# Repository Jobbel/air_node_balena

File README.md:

# air_node
 Software package and hardware for a BalenaOS based air quality sensor node featuring cellular networking, 
 MQTT, GPS localisation, local USB drive data logging and support for the following sensors:
 
 - Alphasense OPC-N3 PM Sensor
 - 2xADS1115 connected to NO-B4,CO-B4,OX-B431,NO2-B43 Alphasense ISBs
 - HYT221 Temperature/Humidity Sensor
 - SHT3x Temperature/Humidity Sensor

Hardware used during developement:

 - Raspberry Pi 4
 - SIM7600 4G Modem/GPS receiver
 - USB Stick for local data storage (needs to be vfat formatted)

Configuration can be done via BalenaCloud environment variables or in src/config_cloudless.py if no cloud will be used.

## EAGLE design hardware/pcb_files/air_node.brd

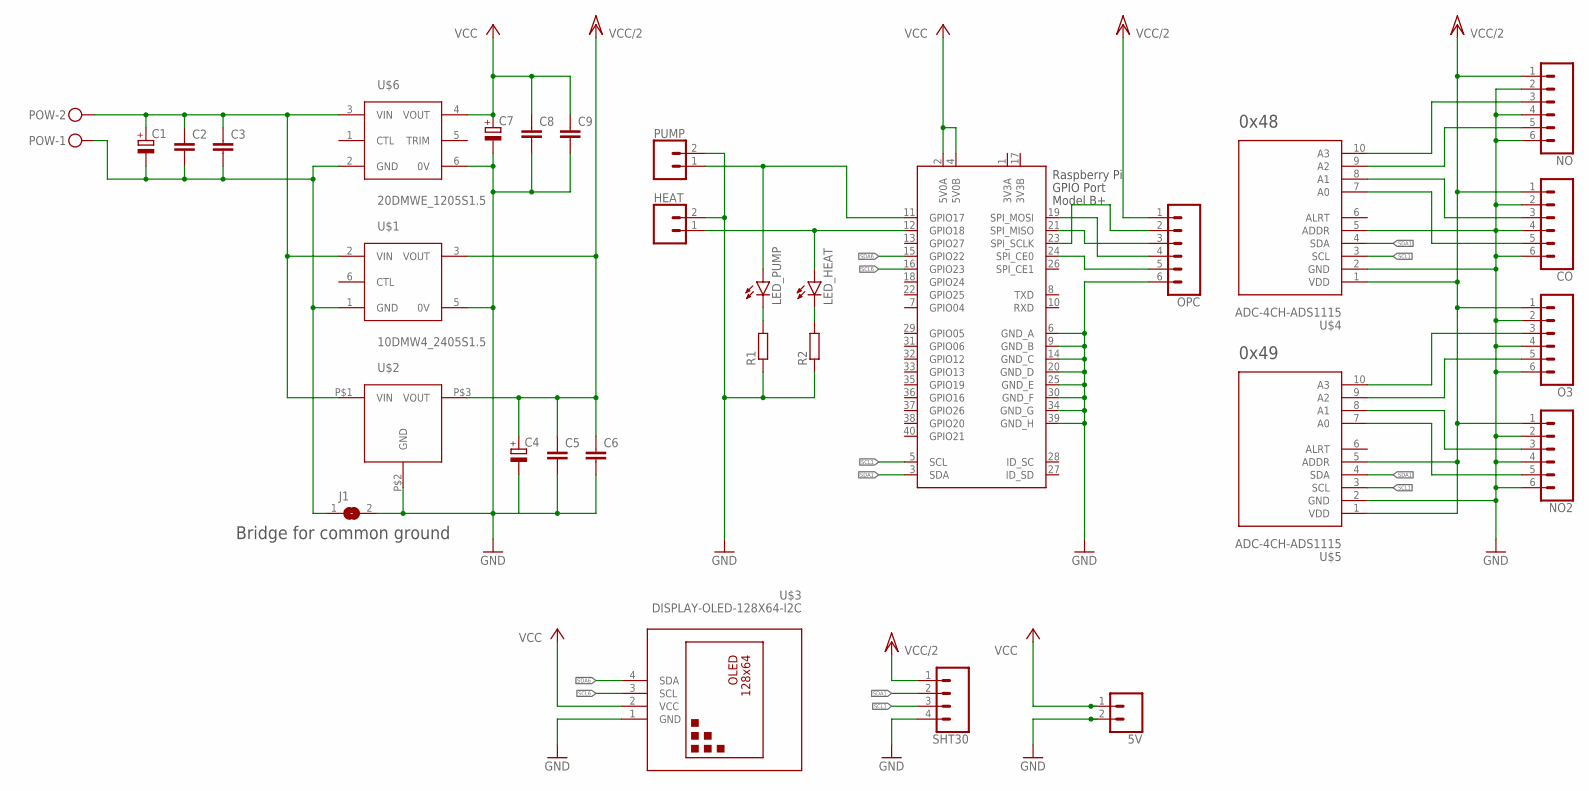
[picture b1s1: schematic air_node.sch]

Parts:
5V: CONN_021X02_NO_SILK; 1X02_NO_SILK
C1, C4, C7: CPOL-EUE3.5-10; E3,5-10
C2, C5, C8: C-EUC1206; C1206
C3, C6, C9: C-EUC0805; C0805
CO: CONN_06NO_SILK_FEMALE_PTH; 1X06_NO_SILK
HEAT: CONN_021X02_NO_SILK; 1X02_NO_SILK
J1: SJ
LED_HEAT: LEDCHIP-LED0805; CHIP-LED0805
LED_PUMP: LEDCHIP-LED0805; CHIP-LED0805
NO, NO2: CONN_06NO_SILK_FEMALE_PTH; 1X06_NO_SILK
O3: CONN_06NO_SILK_FEMALE_PTH; 1X06_NO_SILK
OPC: CONN_06NO_SILK_FEMALE_PTH; 1X06_NO_SILK
POW: MKDSN1,5/2-5,08
PUMP: CONN_021X02_NO_SILK; 1X02_NO_SILK
R1, R2: R-EU_R0805; R0805
SHT30: CONN_041X04_NO_SILK; 1X04_NO_SILK
U$1: 10DMW4_2405S1.5
U$2: LME78_05-1.0
U$3: DISPLAY-OLED-128X64-I2C
U$4, U$5: ADC-4CH-ADS1115
U$6: 20DMWE_1205S1.5
X1: RASPI_BOARD_B+#_E4; RASPI_BOARD_B+_EDGES_4DRILL

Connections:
3V3A: X1.1 (3V3A)
3V3B: X1.17 (3V3B)
12VGND: C1.-, C2.2, C3.2, J1.1, POW.1, U$1.1 (GND), U$6.2 (GND)
+12V: C1.+, C2.1, C3.1, POW.2, U$1.2 (VIN), U$2.P$1 (VIN), U$6.3 (VIN)
GND: 5V.2, C4.-, C5.2, C6.2, C7.-, C8.2, C9.2, CO.2, CO.4, CO.6, HEAT.2, J1.2, NO.2, NO.4, NO.6, NO2.2, NO2.4, NO2.6, O3.2, O3.4, O3.6, OPC.6, PUMP.2, R1.1, R2.1, SHT30.4, U$1.5 (0V), U$2.P$2 (GND), U$3.1 (GND), U$4.2 (GND), U$4.5 (ADDR), U$5.2 (GND), U$6.6 (0V), X1.6 (GND_A), X1.9 (GND_B), X1.14 (GND_C), X1.20 (GND_D), X1.25 (GND_E), X1.30 (GND_F), X1.34 (GND_G), X1.39 (GND_H)
unnamed: HEAT.1, LED_HEAT.A, X1.12 (GPIO18)
unnamed: LED_PUMP.A, PUMP.1, X1.11 (GPIO17)
unnamed: OPC.2, X1.23 (SPI_SCLK)
unnamed: OPC.4, X1.19 (SPI_MOSI)
unnamed: OPC.5, X1.24 (SPI_CE0)
unnamed: OPC.3, X1.21 (SPI_MISO)
unnamed: NO.3, U$4.10 (A3)
unnamed: NO.5, U$4.9 (A2)
unnamed: CO.3, U$4.8 (A1)
unnamed: CO.5, U$4.7 (A0)
unnamed: O3.3, U$5.10 (A3)
unnamed: O3.5, U$5.9 (A2)
unnamed: NO2.3, U$5.8 (A1)
unnamed: NO2.5, U$5.7 (A0)
unnamed: LED_PUMP.C, R1.2
unnamed: LED_HEAT.C, R2.2
SCL1: SHT30.3, U$4.3 (SCL), U$5.3 (SCL), X1.5 (SCL)
SCL6: U$3.3 (SCL), X1.16 (GPIO23)
SDA1: SHT30.2, U$4.4 (SDA), U$5.4 (SDA), X1.3 (SDA)
SDA6: U$3.4 (SDA), X1.15 (GPIO22)
VCC: 5V.1, C7.+, C8.1, C9.1, U$3.2 (VCC), U$6.4 (VOUT), X1.2 (5V0A), X1.4 (5V0B)
VCC/2: C4.+, C5.1, C6.1, CO.1, NO.1, NO2.1, O3.1, OPC.1, SHT30.1, U$1.3 (VOUT), U$2.P$3 (VOUT), U$4.1 (VDD), U$5.1 (VDD), U$5.5 (ADDR)

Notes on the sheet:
0x49
0x48
Bridge for common ground

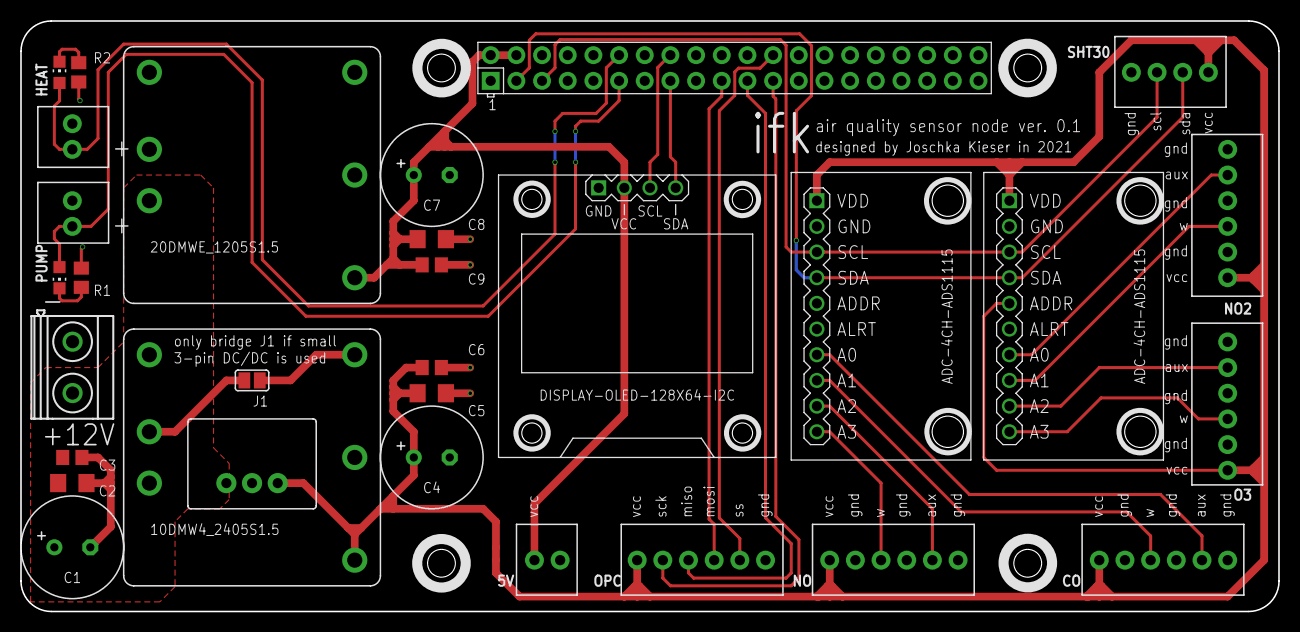
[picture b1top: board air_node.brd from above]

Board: 2 copper layers, 124.5 x 58.4 mm, 31 parts (0 on the bottom side), 25 nets.

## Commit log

2021-08-03 copy from airnode to balenaos
2021-08-12 modem_handler AT exclusive, fsck logger
2021-08-18 major config refactor
    replaced config.yaml with config.py to enable balena cloud environment variable usage
2021-08-18 added two point calibration to sensors
    all sensors inherit from generic_sensor which implements the two point calibration
2021-08-18 changed calibration
    1,1,1,1 will disable any calibration
2021-08-18 config from cloud env
2021-08-19 added second adc, oled fixes
2021-08-20 pid fix gps poll enable flag
2021-08-24 threaded logging
    thread refactor logging and lob config var rename
2021-09-04 added tini as pid1 in the dockerfile
2021-09-04 made system calls silent,failcount starts at 1
2021-10-03 modem, exit, overheat
    removed modem fail counter, catching exit signals, added heater safety shutoff
2021-10-03 logging to /data
2021-10-03 cloudless name back to testnode
2021-10-04 no change
2021-10-06 added usb log sync, rsync params probably wrong
2021-10-14 rsync and env fix
2021-10-14 remount usb and exit handler
2021-10-23 hardcoded temperature n factor
2021-12-06 added RAW ADC and OPC data and config
2022-02-21 fixed timezone local tzlocal package version to avoid console spam
2022-02-21 removed sensitive data
2022-02-21 Create LICENSE
2022-03-23 added stl files
2022-03-23 added more hardware files
2022-03-23 Update README.md
    Added HW overview
2023-01-17 bump debian to bullseye
2023-01-18 Major code refactor
    Refactor all the things
2023-01-20 added rounding to raw data
2023-01-20 removed rsync/uhubctl from start.sh
2023-01-20 reenabled sleep on mm
2023-01-20 added packet counter to mqtt
2023-01-20 added ram usage to metrics
2023-01-20 ensure disabled sht heater
2023-01-20 created internet watchdog
2023-01-20 added rsync call to logging thread
2023-01-20 mqtt disable option, rsync/Internet watchdog
2023-01-20 new IW/log/mqtt config options
2023-01-20 added working bullseye requirements.txt versions
2023-02-06 updated pi/modem holders
    Added cutouts for sim/sd card accessibility
2023-03-01 fixed modem disconnector initial state
2023-03-08 rsync mount check
2023-03-08 reduce adc gain
2023-03-11 updated dockerignore
2023-03-11 removed fs type from mount
2023-03-11 watchdog init print
2023-03-11 fixed rsync mount check
2023-03-11 added default to dict pop
2023-03-11 added new modem device
2023-03-11 slowed gps/removed fix msg
2023-03-11 add usb mounted check
2023-03-13 added fsck to startup script
2023-03-13 cloudflare dns and increased timeout
2023-03-13 watchdog includes modem number
2023-07-20 pcb v0.2
    added one-wire, uart, usb disconnector port and one more ads1115
2023-07-20 added oled port parameter for pi3
2023-07-21 fix startup without sht connected
2023-07-21 event based opc reading without sleep
2023-07-23 increased gps poll interval
    sometimes mmcli times out with the old interval
2023-07-23 catch inhomogenous mean data
    when opc disconnected sometimes the mean data could not be turned into a dataframe
2023-07-23 turn off sht heater and oled pi3 dtoverlay comment
2023-07-23 fixed calculate_mean_data typing
2023-07-24 added one wire heater temp sensor
2023-07-25 first autotuning tests
    does not really work
2023-07-25 fix ku scale
2023-07-30 pid autotuner class
2023-07-30 measure air and heater
2023-08-19 more info on exception
2023-08-19 new heater config
2023-08-19 heater controller with polynomial
2023-08-19 PI controller/docu
2023-08-19 auto thermocouple sensor
2023-08-19 more modem exception logging
2023-08-19 correct convention
2023-08-19 fast modem polling/latlon checks
2023-08-20 catch faulty time/alt
2023-09-01 reduce modem polling speed
2023-09-15 oled scroll fix/wd reminder
2023-10-10 antenna_drill_guide/psu_holder
2023-10-20 adjust modem power pin to hardware v0.2
2023-10-20 increase scroll length to show last line
2023-10-20 fix bug where enable_thermocouple was not initialized but used
2023-10-20 new start script which chooses between sda and sdb for usb drive
2023-10-21 fix offline sensors during startup
2023-11-02 added new model stls
2023-11-07 added grid_mount
2023-12-07 added example connection configs
2024-01-17 add adjustable minimal drying temperature
    Minimal drying temperature to avoid freezing/condensation inside the Container, env var HEATER_MIN_TEMP
2024-03-26 Added PSU cover
    Cover for the exposed terminals of the power supply unit. Requires one heat set insert and M3x10 screw to mount
2024-04-27 freeze requirements to known working versions
2024-04-27 catch all mqtt exceptions
2024-04-27 consistent numpy clip usage
2024-04-27 higher heater shutdown priority
2024-04-27 Added shifted pi holder for small enclosures
2024-08-23 updated airnode cad model
2024-10-14 added dbus based modem handler
    add option to fetch modem and gps data from modemmanager using dbus
2024-10-14 set pid tuner hysteresis delta to 5
    increase default hysteresis delta to 5 degrees as the parameters resulting from a delta of 3.5 degrees were too agressive
2024-10-15 add config option to publish every second
2024-10-15 some hardware files, generated bom and centroid file
2024-10-15 new zip tie modem mount
2024-11-05 use correct type for min heater temp
2024-11-05 publish on every full minute
2025-03-17 fix gps timestamp parsing
2025-03-17 heating pid power limit
2025-03-17 enforce nmea time type
2025-03-18 modem reset before power cycle

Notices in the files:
parts and their libraries:
SparkFun-Connectors: Licensing: Creative Commons ShareAlike 4.0 International - https://creativecommons.org/licenses/by-sa/4.0
diy-modules: Released under the Creative Commons Attribution 4.0 International License: http://creativecommons.org/licenses/by/4.0
